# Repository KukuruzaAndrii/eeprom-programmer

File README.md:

## PCB design
Done in KiCad 9.0

### Scheme
[Scheme](pcb/v1/scheme/eeprom-programmer.pdf)

### PCB
Two versions of PCB placed in repo: regular and with rounded tracks.
Rounded tracks done with [mitxela plugin](https://github.com/mitxela/kicad-round-tracks)

### BOM
[Interactive BOM list](pcb/v1/bom/ibom.html)

### Gergers
For [regular pcb](pcb/v1/gerbers) and [rounded pcb](pcb/v1/gerbers-rounded)

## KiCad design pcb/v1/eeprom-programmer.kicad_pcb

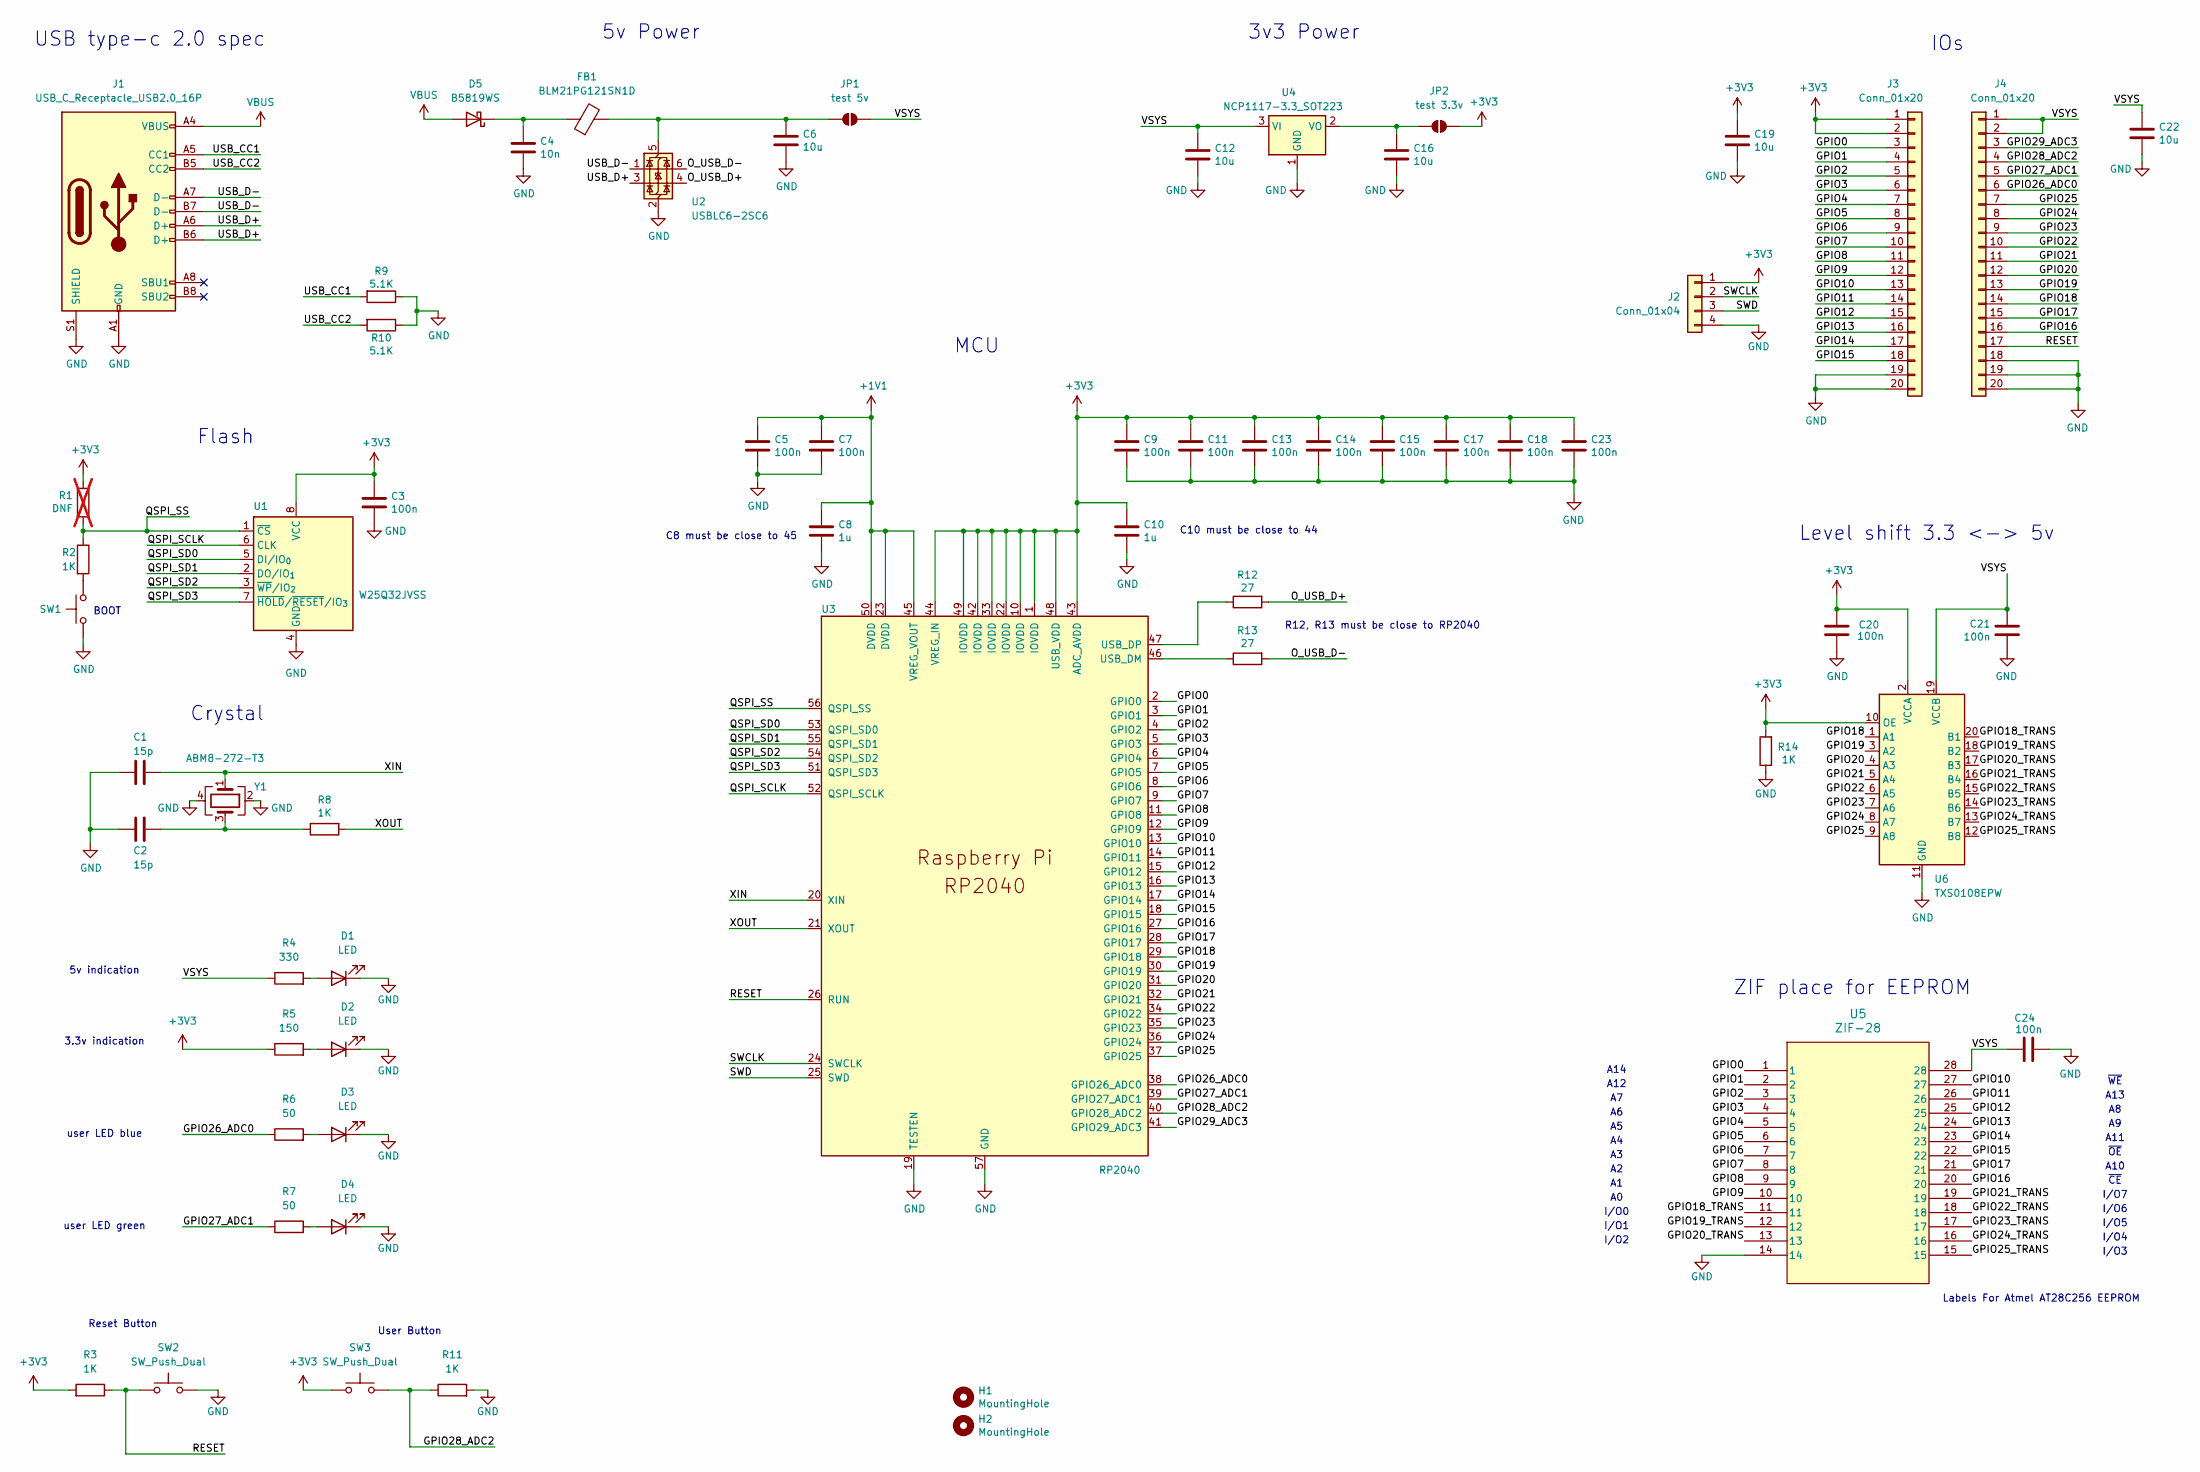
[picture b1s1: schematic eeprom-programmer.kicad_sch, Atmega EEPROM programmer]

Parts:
C1, C2: 15p; C_0603_1608Metric_Pad1.08x0.95mm_HandSolder
C3, C5, C7, C9, C11, C13, C14, C15, C17, C18, C20, C21, C23, C24: 100n; C_0603_1608Metric_Pad1.08x0.95mm_HandSolder
C4: 10n; C_0603_1608Metric_Pad1.08x0.95mm_HandSolder
C6, C12, C16, C19, C22: 10u; C_0603_1608Metric_Pad1.08x0.95mm_HandSolder
C8, C10: 1u; C_0603_1608Metric_Pad1.08x0.95mm_HandSolder
D1, D2, D3, D4: LED; LED_0603_1608Metric_Pad1.05x0.95mm_HandSolder
D5: B5819WS; D_SOD-323_HandSoldering
FB1: BLM21PG121SN1D; L_0805_2012Metric_Pad1.05x1.20mm_HandSolder
H1, H2: MountingHole; MountingHole_2.7mm_M2.5
J1: USB_C_Receptacle_USB2.0_16P; USB_C_Receptacle_GCT_USB4105-xx-A_16P_TopMnt_Horizontal
J2: Conn_01x04; PinHeader_1x04_P2.54mm_Vertical
J3, J4: Conn_01x20; PinHeader_1x20_P2.54mm_Vertical
JP1: test 5v; SolderJumper-2_P1.3mm_Open_RoundedPad1.0x1.5mm
JP2: test 3.3v; SolderJumper-2_P1.3mm_Open_RoundedPad1.0x1.5mm
R1: DNF; R_0603_1608Metric_Pad0.98x0.95mm_HandSolder; not fitted
R2, R3, R8, R11, R14: 1K; R_0603_1608Metric_Pad0.98x0.95mm_HandSolder
R4: 330; R_0603_1608Metric_Pad0.98x0.95mm_HandSolder
R5: 150; R_0603_1608Metric_Pad0.98x0.95mm_HandSolder
R6, R7: 50; R_0603_1608Metric_Pad0.98x0.95mm_HandSolder
R9, R10: 5.1K; R_0603_1608Metric_Pad0.98x0.95mm_HandSolder
R12, R13: 27; R_0603_1608Metric_Pad0.98x0.95mm_HandSolder
SW1, SW2, SW3: SW_Push_Dual; SW_SPST_PTS810
U1: W25Q32JVSS; SOIC-8_5.3x5.3mm_P1.27mm
U2: USBLC6-2SC6; SOT-23-6_Handsoldering
U3: RP2040; RP2040-QFN-56
U4: NCP1117-3.3_SOT223; SOT-223-3_TabPin2
U5: ZIF-28; DIP_Socket-28_W11.9_W12.7_W15.24_W17.78_W18.5_3M_228-1277-0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
U6: TXS0108EPW; TSSOP-20_4.4x6.5mm_P0.65mm
Y1: ABM8-272-T3; Crystal_SMD_Abracon_ABM8G-4Pin_3.2x2.5mm

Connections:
+1V1: C5.1, C7.1, C8.1, U3.23 (DVDD), U3.45 (VREG_VOUT), U3.50 (DVDD)
+3V3: C3.1, C9.1, C10.1, C11.1, C13.1, C14.1, C15.1, C17.1, C18.1, C19.1, C20.2, C23.1, J2.1, J3.1, J3.2, JP2.2 (B), R1.1, R3.2, R5.1, R14.2, SW3.1, U1.8 (VCC), U3.1 (IOVDD), U3.10 (IOVDD), U3.22 (IOVDD), U3.33 (IOVDD), U3.42 (IOVDD), U3.43 (ADC_AVDD), U3.44 (VREG_IN), U3.48 (USB_VDD), U3.49 (IOVDD), U6.2 (VCCA), U6.10 (OE)
/GPIO0: J3.3, U3.2 (GPIO0), U5.1
/GPIO1: J3.4, U3.3 (GPIO1), U5.2
/GPIO2: J3.5, U3.4 (GPIO2), U5.3
/GPIO3: J3.6, U3.5 (GPIO3), U5.4
/GPIO4: J3.7, U3.6 (GPIO4), U5.5
/GPIO5: J3.8, U3.7 (GPIO5), U5.6
/GPIO6: J3.9, U3.8 (GPIO6), U5.7
/GPIO7: J3.10, U3.9 (GPIO7), U5.8
/GPIO8: J3.11, U3.11 (GPIO8), U5.9
/GPIO9: J3.12, U3.12 (GPIO9), U5.10
/GPIO10: J3.13, U3.13 (GPIO10), U5.27
/GPIO11: J3.14, U3.14 (GPIO11), U5.26
/GPIO12: J3.15, U3.15 (GPIO12), U5.25
/GPIO13: J3.16, U3.16 (GPIO13), U5.24
/GPIO14: J3.17, U3.17 (GPIO14), U5.23
/GPIO15: J3.18, U3.18 (GPIO15), U5.22
/GPIO16: J4.16, U3.27 (GPIO16), U5.20
/GPIO17: J4.15, U3.28 (GPIO17), U5.21
/GPIO18: J4.14, U3.29 (GPIO18), U6.1 (A1)
/GPIO18_TRANS: U5.11, U6.20 (B1)
/GPIO19: J4.13, U3.30 (GPIO19), U6.3 (A2)
/GPIO19_TRANS: U5.12, U6.18 (B2)
/GPIO20: J4.12, U3.31 (GPIO20), U6.4 (A3)
/GPIO20_TRANS: U5.13, U6.17 (B3)
/GPIO21: J4.11, U3.32 (GPIO21), U6.5 (A4)
/GPIO21_TRANS: U5.19, U6.16 (B4)
/GPIO22: J4.10, U3.34 (GPIO22), U6.6 (A5)
/GPIO22_TRANS: U5.18, U6.15 (B5)
/GPIO23: J4.9, U3.35 (GPIO23), U6.7 (A6)
/GPIO23_TRANS: U5.17, U6.14 (B6)
/GPIO24: J4.8, U3.36 (GPIO24), U6.8 (A7)
/GPIO24_TRANS: U5.16, U6.13 (B7)
/GPIO25: J4.7, U3.37 (GPIO25), U6.9 (A8)
/GPIO25_TRANS: U5.15, U6.12 (B8)
/GPIO26_ADC0: J4.6, R6.1, U3.38 (GPIO26_ADC0)
/GPIO27_ADC1: J4.5, R7.1, U3.39 (GPIO27_ADC1)
/GPIO28_ADC2: J4.4, R11.1, SW3.2, U3.40 (GPIO28_ADC2)
/GPIO29_ADC3: J4.3, U3.41 (GPIO29_ADC3)
/O_USB_D+: R12.2, U2.4 (I/O2)
/O_USB_D-: R13.2, U2.6 (I/O1)
/QSPI_SCLK: U1.6 (CLK), U3.52 (QSPI_SCLK)
/QSPI_SD0: U1.5 (DI/IO_{0}), U3.53 (QSPI_SD0)
/QSPI_SD1: U1.2 (DO/IO_{1}), U3.55 (QSPI_SD1)
/QSPI_SD2: U1.3 (~WP/IO_{2}), U3.54 (QSPI_SD2)
/QSPI_SD3: U1.7 (~HOLD/~RESET/IO_{3}), U3.51 (QSPI_SD3)
/QSPI_SS: R1.2, R2.1, U1.1 (~CS), U3.56 (QSPI_SS)
/RESET: J4.17, R3.1, SW2.1, U3.26 (RUN)
/SWCLK: J2.2, U3.24 (SWCLK)
/SWD: J2.3, U3.25 (SWD)
/USB_CC1: J1.A5 (CC1), R9.2
/USB_CC2: J1.B5 (CC2), R10.2
/USB_D+: J1.A6 (D+), J1.B6 (D+), U2.3 (I/O2)
/USB_D-: J1.A7 (D-), J1.B7 (D-), U2.1 (I/O1)
/VSYS: C12.1, C21.1, C22.1, C24.1, J4.1, J4.2, JP1.2 (B), R4.1, U4.3 (VI), U5.28, U6.19 (VCCB)
/XIN: C1.2, U3.20 (XIN), Y1.1
/XOUT: R8.2, U3.21 (XOUT)
GND: C1.1, C2.2, C3.2, C4.2, C5.2, C6.2, C7.2, C8.2, C9.2, C10.2, C11.2, C12.2, C13.2, C14.2, C15.2, C16.2, C17.2, C18.2, C19.2, C20.1, C21.2, C22.2, C23.2, C24.2, D1.1 (K), D2.1 (K), D3.1 (K), D4.1 (K), J1.A1 (GND), J1.A12 (GND), J1.B1 (GND), J1.B12 (GND), J1.S1 (SHIELD), J2.4, J3.19, J3.20, J4.18, J4.19, J4.20, R9.1, R10.1, R11.2, R14.1, SW1.1, SW2.2, U1.4 (GND), U2.2 (GND), U3.19 (TESTEN), U3.57 (GND), U4.1 (GND), U5.14, U6.11 (GND), Y1.2, Y1.4
unnamed: C2.1, R8.1, Y1.3
unnamed: D1.2 (A), R4.2
unnamed: D2.2 (A), R5.2
unnamed: D3.2 (A), R6.2
unnamed: D4.2 (A), R7.2
unnamed: C4.1, D5.1 (K), FB1.1
unnamed: C6.1, FB1.2, JP1.1 (A), U2.5 (VBUS)
unnamed: C16.1, JP2.1 (A), U4.2 (VO)
unnamed: R2.2, SW1.2
unnamed: R13.1, U3.46 (USB_DM)
unnamed: R12.1, U3.47 (USB_DP)
VBUS: D5.2 (A), J1.A4 (VBUS), J1.A9 (VBUS), J1.B4 (VBUS), J1.B9 (VBUS)

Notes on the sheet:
A11
A10
Labels For Atmel AT28C256 EEPROM
IOs
5v Power
~{CE}
3v3 Power
Crystal
I/O2
Level shift 3.3 <-> 5v
MСU
C8 must be close to 45
I/O3
I/O4
I/O6
A12
USB type-c 2.0 spec
user LED green
I/O5
User Button
BOOT
C10 must be close to 44
5v indication
user LED blue
A13
I/O1
I/O0
3.3v indication
Reset Button
R12, R13 must be close to RP2040
ZIF place for EEPROM
A14
~{OE}
Flash
I/O7
~{WE}

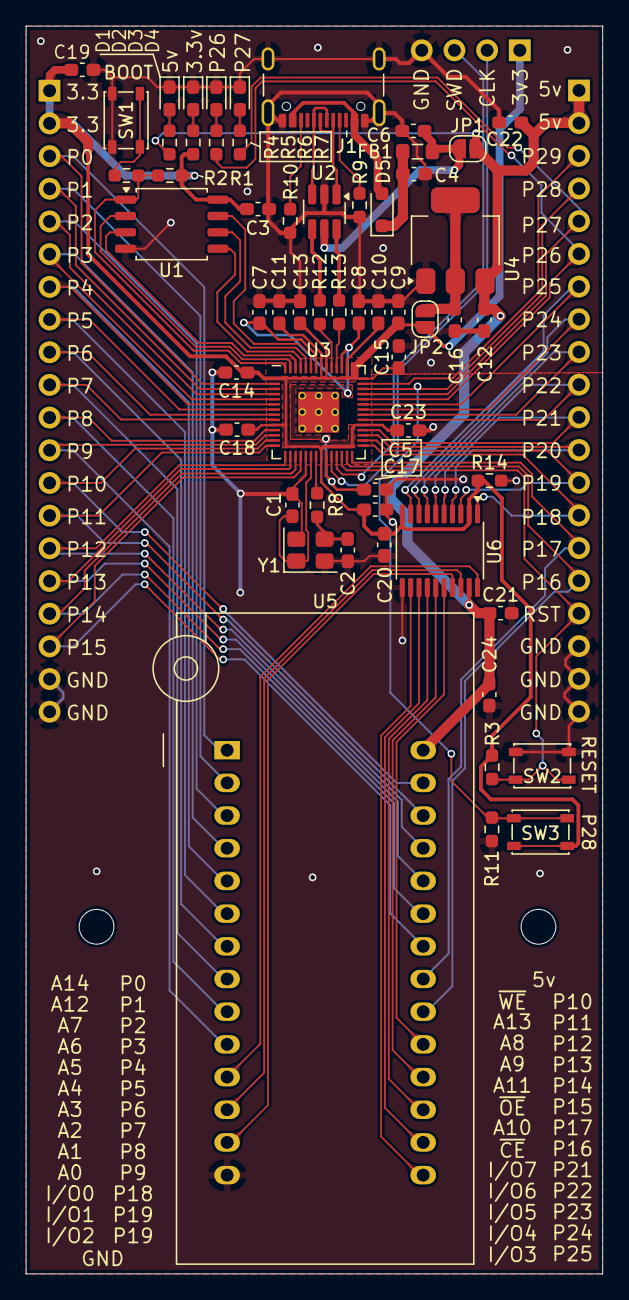
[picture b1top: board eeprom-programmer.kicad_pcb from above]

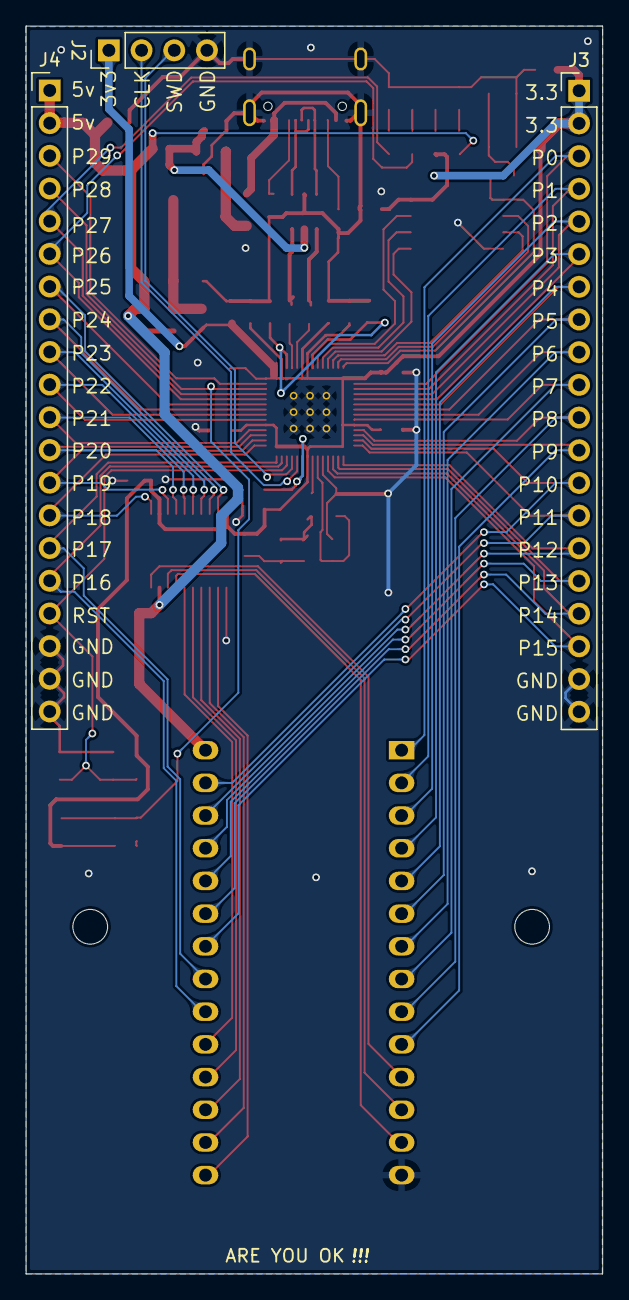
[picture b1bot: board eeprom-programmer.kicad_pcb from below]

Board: 2 copper layers, 44.8 x 97.0 mm, 62 parts (3 on the bottom side), 71 nets.

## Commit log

2025-07-10 init; add pcb v1
2025-08-26 fix 2 mixed up labels; update output files; add pcb with rounded labels
2025-08-26 add README
2025-08-31 add init project for rp2040
